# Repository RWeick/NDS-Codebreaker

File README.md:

# NDS-Codebreaker
The full schematic, gerbers, and flash rom dump of the Nintendo DS Codebreaker

PCB Thickness: 0.8 mm

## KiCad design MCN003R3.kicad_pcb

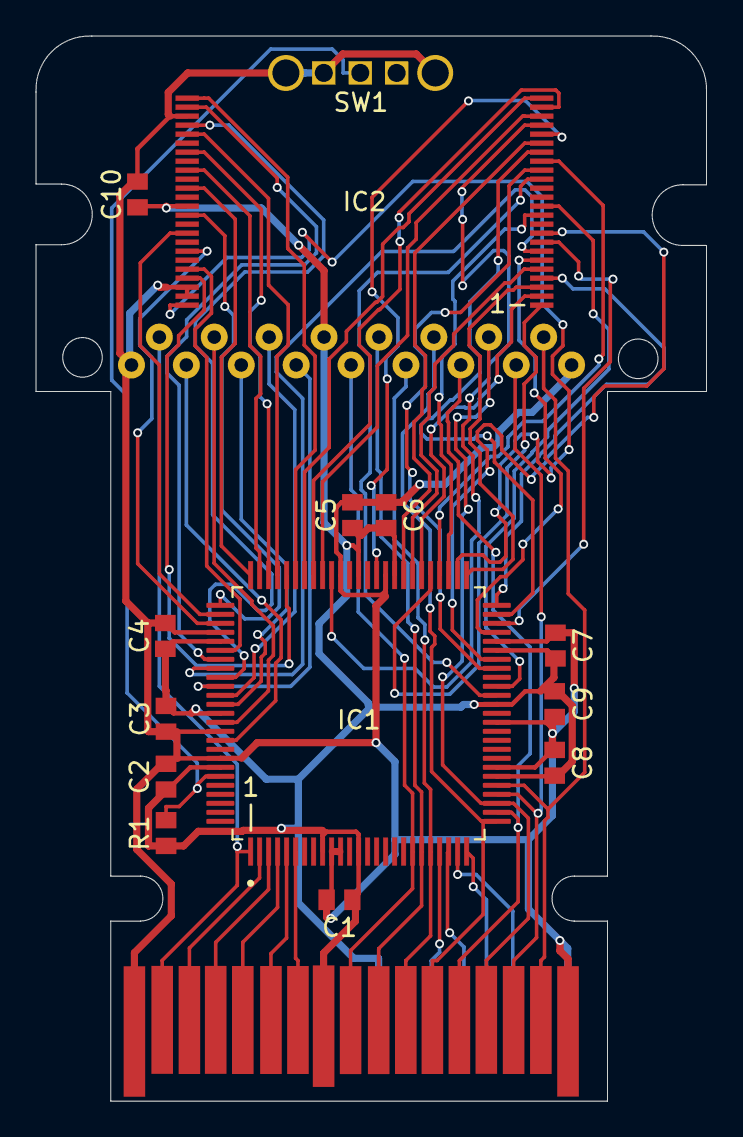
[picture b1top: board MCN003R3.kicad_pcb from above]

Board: 2 copper layers, 37.2 x 59.2 mm, 19 parts (1 on the bottom side), 60 nets.

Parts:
C1, C2, C3, C4, C5, C6, C7, C8, C9, C10: C_Small; SMD Component
Hole1, Hole2: MountingHole_2.2mm_M2
IC1: EPM570T100; ACTEL FPGA
IC2: ES29LV160EB; SOP50P2000X120-48N
J1: NDS_Front_Edge_Connector; Edge Connector
J2: NDS_Cart_Slot; Cart Connector
J3: Rear_Side_JTAG_Edge_Connector; Edge Connector
R1: R_Small_US; SMD Component
SW1: SW_SPDT; Slide Switch

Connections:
/CLK: IC1.1 (IO2_1), J1.2 (CLK), J2.2 (CLK)
/DS.Cart.CS1: IC1.89 (IO2_89), J2.4 (CS1)
/DS.Cart.CS2: IC1.86 (IO2_86), J2.6 (CS2)
/DS.Cart.IRQ: IC1.85 (IO2_85), J2.7 (IRQ)
/DS.Cart.Pin3: IC1.91 (IO2_91), J2.3 (N/C)
/DS.Cart.Reset: IC1.87 (IO2_87), J2.5 (Reset)
/DS.D0: IC1.19 (IO1_19), J1.9 (D0), J2.9 (D0)
/DS.D1: IC1.20 (IO1_20), J1.10 (D1), J2.10 (D1)
/DS.D2: IC1.21 (IO1_21), J1.11 (D2), J2.11 (D2)
/DS.D3: IC1.26 (IO1_26), J1.12 (D3), J2.12 (D3)
/DS.D4: IC1.27 (IO1_27), J1.13 (D4), J2.13 (D4)
/DS.D5: IC1.28 (IO1_28), J1.14 (D5), J2.14 (D5)
/DS.D6: IC1.29 (IO1_29), J1.15 (D6), J2.15 (D6)
/DS.D7: IC1.30 (IO1_30), J1.16 (D7), J2.16 (D7)
/DS.Edge.CS1: IC1.3 (IO1_3), J1.4 (CS1)
/DS.Edge.CS2: IC1.5 (IO1_5), J1.6 (CS2)
/DS.Edge.IRQ: IC1.6 (IO1_6), J1.7 (IRQ)
/DS.Edge.Pin3: IC1.2 (IO1_2), J1.3 (N/C)
/DS.Edge.Reset: IC1.4 (IO1_4), J1.5 (Reset)
/EXCELSEMI.A0: IC1.70 (IO2_70), IC2.25 (A0)
/EXCELSEMI.A1: IC1.69 (IO2_69), IC2.24 (A1)
/EXCELSEMI.A2: IC1.68 (IO2_68), IC2.23 (A2)
/EXCELSEMI.A3: IC1.67 (IO2_67), IC2.22 (A3)
/EXCELSEMI.A4: IC1.66 (IO2_66), IC2.21 (A4)
/EXCELSEMI.A5: IC1.61 (IO2_61), IC2.20 (A5)
/EXCELSEMI.A6: IC1.58 (IO2_58), IC2.19 (A6)
/EXCELSEMI.A7: IC1.49 (IO1_49), IC2.18 (A7)
/EXCELSEMI.A8: IC1.48 (IO1_48), IC2.8 (A8)
/EXCELSEMI.A9: IC1.83 (IO2_83), IC2.7 (A9)
/EXCELSEMI.A10: IC1.47 (IO1_47), IC2.6 (A10)
/EXCELSEMI.A11: IC1.57 (IO2_57), IC2.5 (A11)
/EXCELSEMI.A12: IC1.50 (IO1_50), IC2.4 (A12)
/EXCELSEMI.A13: IC1.51 (IO1_51), IC2.3 (A13)
/EXCELSEMI.A14: IC1.56 (IO2_56), IC2.2 (A14)
/EXCELSEMI.A15: IC1.55 (IO2_55), IC2.1 (A15)
/EXCELSEMI.A16: IC1.52 (IO2_52), IC2.48 (A16)
/EXCELSEMI.A17: IC1.54 (IO2_54), IC2.17 (A17)
/EXCELSEMI.A18: IC1.43 (IO1_43/DEV_OE), IC2.16 (A18)
/EXCELSEMI.A19: IC1.44 (IO1_44/DEV_CLRn), IC2.9 (A19)
/EXCELSEMI.A-1: IC1.71 (IO2_71), IC2.45 (DQ15/A-1)
/EXCELSEMI.CE: IC1.82 (IO2_82), IC2.26 (CE#)
/EXCELSEMI.DQ0: IC1.72 (IO2_72), IC2.29 (DQ0)
/EXCELSEMI.DQ1: IC1.73 (IO2_73), IC2.31 (DQ1)
/EXCELSEMI.DQ2: IC1.74 (IO2_74), IC2.33 (DQ2)
/EXCELSEMI.DQ3: IC1.75 (IO2_75), IC2.35 (DQ3)
/EXCELSEMI.DQ4: IC1.76 (IO2_76), IC2.38 (DQ4)
/EXCELSEMI.DQ5: IC1.77 (IO2_77), IC2.40 (DQ5)
/EXCELSEMI.DQ6: IC1.78 (IO2_78), IC2.42 (DQ6)
/EXCELSEMI.DQ7: IC1.81 (IO2_81), IC2.44 (DQ7)
/EXCELSEMI.OE: IC1.84 (IO2_84), IC2.28 (OE#)
/EXCELSEMI.RESET: IC1.41 (IO1_41), IC2.12 (RESET#)
/EXCELSEMI.RY-BY: IC1.40 (IO1_40), IC2.15 (RY/BY#)
/EXCELSEMI.WE: IC1.53 (IO2_53), IC2.11 (WE#)
/GND: C1.1, C2.2, C3.1, C4.2, C5.2, C6.2, C7.2, C8.2, C9.1, C10.2, IC1.10 (GNDIO), IC1.11 (GNDINT), IC1.32 (GNDIO), IC1.37 (GNDINT), IC1.46 (GNDIO), IC1.60 (GNDIO), IC1.65 (GNDINT), IC1.79 (GNDIO), IC1.90 (GNDINT), IC1.93 (GNDIO), IC2.27 (VSS), IC2.46 (VSS), IC2.47 (BYTE#), J1.1 (GND), J1.17 (GND), J2.1 (GND), J2.17 (GND), J3.1 (GND), SW1.1 (A), SW1.4 (Shield), SW1.5 (Shield)
/Switch: IC1.95 (IO2_95), R1.2, SW1.2 (B)
/TCK: IC1.24 (TCK), J3.3 (N/C)
/TDI: IC1.23 (TDI), J3.5 (Reset)
/TDO: IC1.25 (TDO), J3.4 (CS1)
/TMS: IC1.22 (TMS), J3.6 (CS2)
/VCC: C1.2, C2.1, C3.2, C4.1, C5.1, C6.1, C7.1, C8.1, C9.2, C10.1, IC1.9 (VCCIO1), IC1.13 (VCCINT), IC1.31 (VCCIO1), IC1.39 (VCCINT), IC1.45 (VCCIO1), IC1.59 (VCCIO2), IC1.63 (VCCINT), IC1.80 (VCCIO2), IC1.88 (VCCINT), IC1.94 (VCCIO2), IC2.37 (VCC), J1.8 (VCC), J2.8 (VCC), J3.8 (VCC), R1.1
